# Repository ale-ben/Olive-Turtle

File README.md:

- [1. Olive-Turtle](#1-olive-turtle)
- [2. Final Result](#2-final-result)
	- [2.1. Dashboard](#21-dashboard)
	- [2.2. Debug Dashboard](#22-debug-dashboard)
- [3. Required components and software](#3-required-components-and-software)
	- [3.1. Home Assistant](#31-home-assistant)
		- [3.1.1. Hardware](#311-hardware)
		- [3.1.2. Software](#312-software)
	- [3.2. MicroController](#32-microcontroller)
		- [3.2.1. Hardware](#321-hardware)
		- [3.2.2. Software](#322-software)
- [4. Installation and wiring](#4-installation-and-wiring)
	- [4.1. Home Assistant](#41-home-assistant)
	- [4.2. Microcontroller](#42-microcontroller)
		- [4.2.1. Wiring](#421-wiring)
		- [4.2.2. Software](#422-software)
			- [4.2.2.1. Test Software](#4221-test-software)
			- [4.2.2.2. ESPHome integration](#4222-esphome-integration)
- [5. Telegram Bot](#5-telegram-bot)
	- [5.1. Bot Configuration](#51-bot-configuration)
	- [5.2. Commands](#52-commands)
- [6. Future Development](#6-future-development)
	- [6.1. Hardware Side](#61-hardware-side)
	- [6.2. Software Side](#62-software-side)

# 1. Olive-Turtle

 Turtle as a logo, no background, realistic")

Olive Turtle is a project developed for the "Laboratory of Making" course (2022/2023) taught by Professor Renzo Davoli and Professor Federico Montori at the University of Bologna.

The project aims to implement a board capable of controlling a 12V LED strip with brightness control and environmental data acquisition.

Everything is controlled using Home Assistant, an open source software written in Python and released in 2013 under the Apache 2.0 license. It is a complete home automation system that can integreate with most existing IoT and home automation devices (mainly thanks to the huge user base) and be used to control and automate all the devices in your home, including custom made microcontroller boards.

# 2. Final Result

## 2.1. Dashboard

> Note that due to technical problems with the sensors air quality values are not available in this screenshot.

The resulting dashboard integrates the existing "smart lights" (Ikea TRADFRI) and the Olive Turtle board, which is used to control the LED strip and acquire environmental data.

The board allows for a quick glance at the system status or a more detailed view of the data, and it can be used to control the LED strip brightness.

## 2.2. Debug Dashboard

In the debug section you can see raw data from the board along with some debug parameters like WiFi signal strength.

# 3. Required components and software

## 3.1. Home Assistant
### 3.1.1. Hardware
- Raspberry PI 3 (or newer). Note that Home Assistant specifically says that PI 3 is borderline supported due to the limited resources, but it works fine for this project.
### 3.1.2. Software
- [Home Assistant](https://www.home-assistant.io/installation/)
- [Raspberry PI Imager](https://www.raspberrypi.org/software/)

## 3.2. MicroController
### 3.2.1. Hardware
- ESP32 (or any other microcontroller capable of WiFi communication)
- Sensors
  - BMP280
  - ENS160+AHT2x
- LED Control
  - IRF520N MOSFET
  - TLP621 Optocoupler
  - Various resistors
- LED strip with 12V power supply
### 3.2.2. Software
- [Python3](https://www.python.org/downloads/)
- [PlatformIO](https://platformio.org/platformio-ide)
- [ESPHome CLI](https://esphome.io/guides/getting_started_command_line.html)

# 4. Installation and wiring
## 4.1. Home Assistant
If you are using Home Assistant, installation is pretty straight forward, in PI Imager OS selection choose _other specific-purpose OS_, then _Home Assistant and Home Automation_ and finally _Home Assistant_, configure Wireless (If needed) and flash the image on the SD card.

Home Assistant will be available after a couple of minutes at `http://homeassistant.local:8123` (or `http://<ip_address>:8123` if you don't have mDNS enabled on your network).

> Home Assistant is a very complex software, and it's not the focus of this guide, so I won't go into details on how to configure it, but you can find a lot of guides on the internet.

Once installed, you can install ESPHome from the Home Assistant Add-on Store, and then you can start configuring your ESP32 board:
1. Go to the ESPHome tab in Home Assistant sidebar
2. Click on the + button in the bottom right corner
3. Give the board a name
4. Select the board type (ESP32)

ESPHome will generate a configuration file for you and prepare everything for the first upload.

> Note that theoretically the microcontroller setup could be done entirely from this page but it is not a viable option in this specific case due to two problems:
> - We have a component not available (yet) in the ESPHome library;
> - In my tests I noticed that Raspberry PI 3 does not have enough power to compile and upload the code to the board (would probavly work with a Raspberry PI 4).

## 4.2. Microcontroller

### 4.2.1. Wiring
This repository provides both a wiring diagram and a proposed implementation for splitting the component across multiple protoboards.

The `schematics` folder contains the KiCAD project for the wiring diagram and the VeroRoute project for the protoboard implementation. The wiring is consistent between the two projects.

The wiring diagram is split in three sections, the first one contains the microcontroller and relative connections, the second the sensors and I2C connections to the controller and the third the LED strip and relative connections.

This is the proposed implementation for the protoboard, all sensor identification codes refer to the one used in the KiCAD schematic:
> Note that all images have a mirrored version, so that you can use them as a reference when soldering the components on the back of the board. This version can be found in the `schematics/Olive-Turtle_VeroRoute/png` folder.

**Main Board**

**Sensor Board**

**LED Board**

### 4.2.2. Software

#### 4.2.2.1. Test Software
The `Olive-Turtle_manual_control` folder contains a simple test software that can be used to verify that all the components are working correctly.

Make sure to have PlatformIO installed and open the project folder, then using the PlatformIO UI you can compile and upload the code to the board.

This version of the software does not have any WiFi or Home Assistant integration, it simply reads the sensors and allows you to control the LED strip using the serial monitor.
After setup complete this is the list of available commands:
- `help`: Print the list of available commands
- `led <value>`: Set the LED brightness to the specified value (0-255)
- `led`: Print the current LED brightness
- `aht` | `bmp` | `ens`: Print the current value of the specified sensor
- `all`: Print the current value of all the sensors

After verifying that all sensors provide correct values and that the LED strip is working, you can proceed to the next step and configure the board to work with Home Assistant.

> Note that the test software is not required for the next step, it is only provided as a way to verify that all the components are working correctly.

#### 4.2.2.2. ESPHome integration

This is the final step, we will now configure the board to work with Home Assistant.

Open the `Olive-Turtle_esphome` folder, rename (or copy) the secretsTemplate.yaml to secrets.yaml and fill in the required information.
One of the fields will be `homeassistant_key`, this key can be found in Home Assistant, in the ESPHome tab by clicking on the three dots next to the board name and then on _Show API Key.

Once you have filled in all the required information, you can compile and upload the code to the board with `esphome run Olive-Turtle.yaml`.
> Note that the first upload MUST be done using a USB cable, after the first upload you can use OTA updates.

If everything went correctly you should see the board as online in Home Assistant. Next go to settings and add the board as a device. The board will be automatically added to the auto generated dashboard and you can now control the LED strip and see the sensor values.

# 5. Telegram Bot
As a proof of concept I tried implementing a Telegram Bot ([@OliveTurtleBot](https://t.me/OliveTurtleBot)) using the Telegram extension of Home Assistant.

The bot is very simple, it allows you to activate two predefined scenes, __away__ and __nightpc__, but can also be used to get notifications from other Home Assitant automations.

Unfortunately the Telegram extension does not have a UI setup process, so you have to manually edit the configuration file, but it is not very complicated and is explained in the [official documentation](https://www.home-assistant.io/integrations/telegram).

## 5.1. Bot Configuration
The first step is to edit `/config/configuration.yaml` and add the following lines while replacing the placeholders (elements between [[  ]] ) with your data:
```yaml
# Telegram Bot
telegram_bot:
  - platform: polling
    api_key: "[[ API KEY ]]"
    allowed_chat_ids:
      - [[ CHAT ID ]]

# Notifier
notify:
  - platform: telegram
    name: "[[ NAME ]]" # This can be anything you want, will be used internally when calling in automations
    chat_id: [[ CHAT ID]]
```

By adding this to configuration we set up two things:

1. We enable the Telegram Bot extension and configure it to use polling (instead of webhooks) and we specify the API key (provided by [@BotFather](https://t.me/BotFather)) and the chat ID (if you don't know your chat id, use [@getidsbot](https://t.me/getidsbot)).
2. We set up a notify action that we can use in our automations. This will allow us to send messages from the bot to a specific user (as per telegram rules, the user MUST have started the bot first).

After this we need to reload Home Assistant YAML, we can do so from the YAML tab by pressing restart and quick restart.

To test notifications you can use the developer tools in Home Assistant, go to the services tab and select `notify.[[ NAME ]]` from the dropdown menu, then fill in the message and click on call service. You should receive a message from the bot.

Now the bot is able to send messages to the user but it ignores everything received from the user.

## 5.2. Commands
The bot is able to receive commands from the user, but it needs to know what to do with them. To do this we need to add a new automation.

For the sake of this documentation, we will only implement the __ping__ command since th implementation is the same for all the other commands.

Despite what the [official documentation](https://www.home-assistant.io/integrations/telegram_bot/#event-triggering) says, it's easier to configure this from the UI rather than from the automation file.
To do so, go to settings and then to automations, click on the + button, create new automation and select the following options:
- As trigger select a manual trigger
  - insert `telegram_command` as event type
  - insert `command: /ping` as event data
- As action select call service
  - select `Notifications: Send a notification with [[name]]`
  - as message write `pong`

Click save in the bottom right corner and give it a name, once this is done you can test the command by sending `/ping` to the bot.

If you want the bot to suggest available commands you can manually set them using [@BotFather](https://t.me/BotFather).

To make a command that activates a scene you just have to add a second action in your automation and select scene as you can see in the following image:

# 6. Future Development
## 6.1. Hardware Side
- [ ] https://github.com/ale-ben/Olive-Turtle/issues/4 Fix Air quality sensor or identify valid alternative
- [ ] Prototype and print first PCB version
## 6.2. Software Side
- [ ] As soon as https://github.com/esphome/esphome/pull/4243 is merged, remove custom ENS160 implementation and use library instead
  - Removing the custom implementation would also allow to upload directly from Home Assistant (with a more powerful server) therefore removing entirely the need for ESPHome CLI
- [X] Implement InfluxDB as long term sensor data storage
- [ ] Implement Grafana as a dashboard alternative

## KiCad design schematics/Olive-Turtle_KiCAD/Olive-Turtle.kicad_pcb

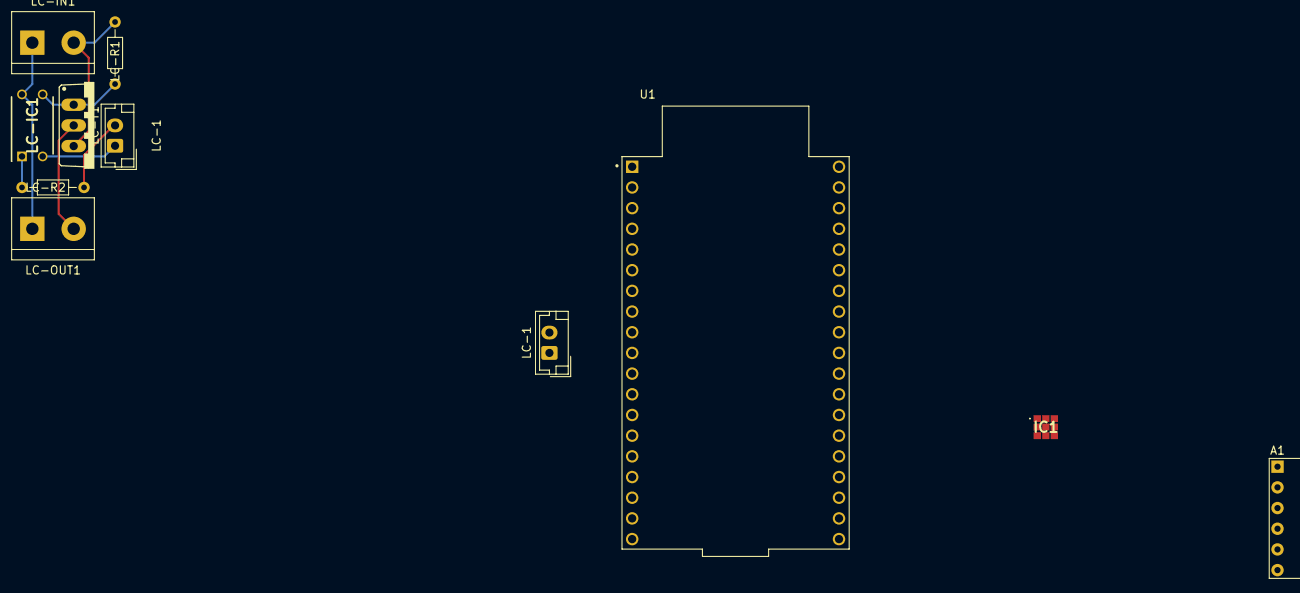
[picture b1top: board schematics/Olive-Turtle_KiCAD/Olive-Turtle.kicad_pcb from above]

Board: 2 copper layers, 11 parts (0 on the bottom side), 13 nets.

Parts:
A1: BMP280_Module
IC1: ENS160-BGLT; ENS160BGLT
LC-1, LC-1#2: JST 2.5mm 2P Wafer; JST_EH_B2B-EH-A_1x02_P2.50mm_Vertical
LC-IC1: TLP621; DIP762W60P254L460H450Q4N
LC-IN1: Screw_Terminal_01x02; TerminalBlock_bornier-2_P5.08mm
LC-OUT1: Screw_Terminal_01x02; TerminalBlock_bornier-2_P5.08mm
LC-R1: 2.2k R; R_Axial_DIN0204_L3.6mm_D1.6mm_P7.62mm_Horizontal
LC-R2: 330 R; R_Axial_DIN0204_L3.6mm_D1.6mm_P7.62mm_Horizontal
LC-T1: IRF520; TO220BV
U1: ESP32-DEVKITC-32U; MODULE_ESP32-DEVKITC-32U

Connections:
/LC1-G: LC-1#2.1, U1.14 (GND1)
/LC1-S: LC-1#2.2, U1.6 (IO35)
/LED Control/12V: LC-IC1.4 (C), LC-IN1.1, LC-OUT1.1
/LED Control/GND: LC-IN1.2, LC-R1.1, LC-T1.S
/LED Control/LC-G: LC-1.1, LC-IC1.2 (K)
/LED Control/LC-S: LC-1.2, LC-R2.2
/SCL: A1.3 (SCL), IC1.2 (SCLK_/_SCL), U1.36 (IO22)
/SDA: A1.4 (SDA), IC1.1 (MOSI_/_SDA), U1.33 (IO21)
unnamed: A1.2 (GND), IC1.8 (VSS_1), U1.38 (GND3)
unnamed: A1.1 (VCC), IC1.5 (VDDIO), U1.1 (3V3)
unnamed: LC-IC1.1 (A), LC-R2.1
unnamed: LC-IC1.3 (E), LC-R1.2, LC-T1.G
unnamed: LC-OUT1.2, LC-T1.D

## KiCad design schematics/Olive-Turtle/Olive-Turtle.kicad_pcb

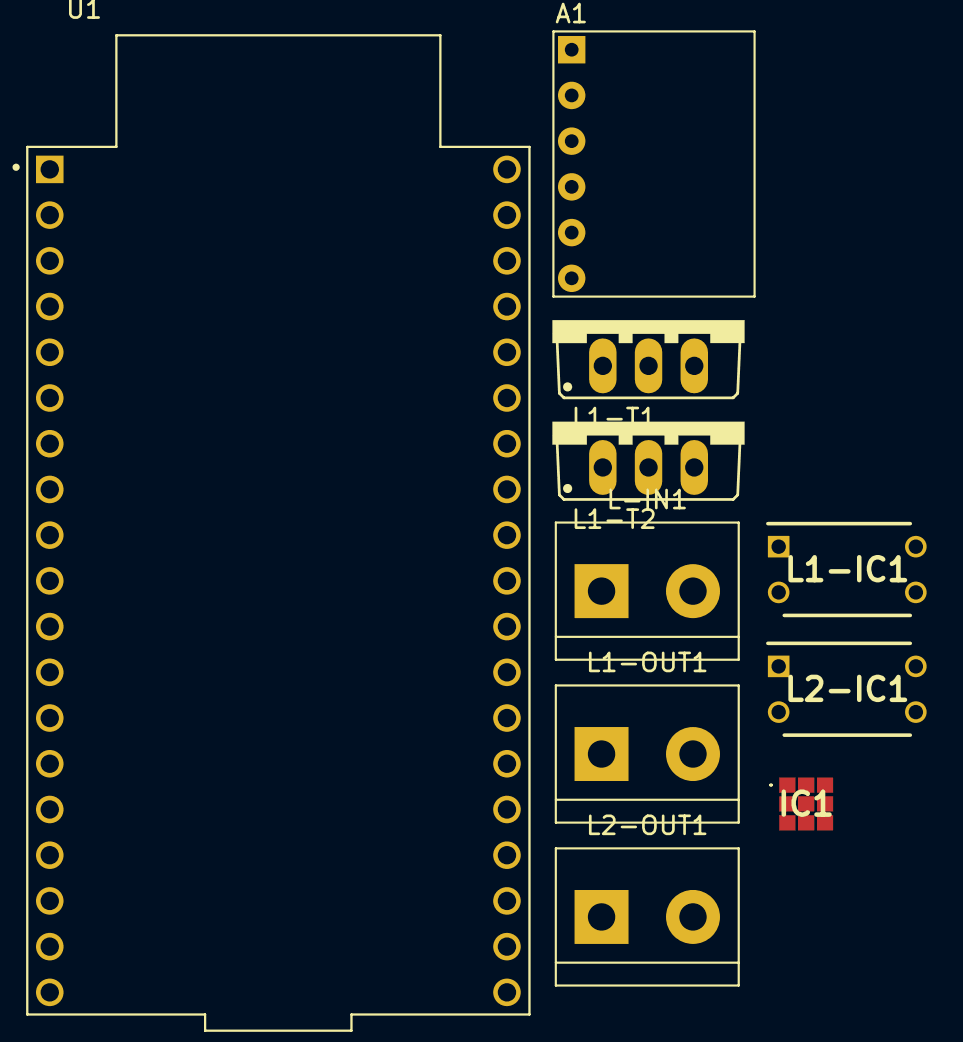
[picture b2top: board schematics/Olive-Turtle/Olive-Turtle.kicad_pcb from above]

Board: 2 copper layers, 10 parts (0 on the bottom side), 11 nets, no tracks yet.

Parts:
A1: BMP280_Module
IC1: ENS160-BGLT; ENS160BGLT
L1-IC1, L2-IC1: TLP621; DIP762W60P254L460H450Q4N
L1-OUT1, L2-OUT1: Screw_Terminal_01x02; TerminalBlock_bornier-2_P5.08mm
L1-T1, L1-T2: IRF520; TO220BV
L-IN1: Screw_Terminal_01x02; TerminalBlock_bornier-2_P5.08mm
U1: ESP32-DEVKITC-32U; MODULE_ESP32-DEVKITC-32U

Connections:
/12V: L1-IC1.4 (C), L1-OUT1.1, L2-IC1.4 (C), L2-OUT1.1, L-IN1.1
/GND: L1-T1.S, L1-T2.S, L-IN1.2
/SCL: A1.3 (SCL), IC1.2 (SCLK_/_SCL), U1.36 (IO22)
/SDA: A1.4 (SDA), IC1.1 (MOSI_/_SDA), U1.33 (IO21)
unnamed: A1.2 (GND), IC1.8 (VSS_1), U1.38 (GND3)
unnamed: A1.1 (VCC), IC1.5 (VDDIO), U1.1 (3V3)
unnamed: L1-IC1.3 (E), L1-T2.G
unnamed: L1-IC1.2 (K), L2-IC1.2 (K), U1.14 (GND1)
unnamed: L1-OUT1.2, L1-T2.D
unnamed: L1-T1.G, L2-IC1.3 (E)
unnamed: L1-T1.D, L2-OUT1.2

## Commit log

2023-09-11 [develop] Project restart
2023-09-11 Designed VeeCAD schematic
2023-09-12 [develop] Schematic for LC
2023-09-18 [develop] Update Kicad schematic
2023-09-19 [develop] Reset OT manual control
2023-09-19 [develop] Remove old schematics
2023-09-19 [develop] Get & set LED PWM
2023-09-19 [develop] Working ?
2023-09-19 [develop] Move LED1 to pin 32 since 35 is input only
2023-09-19 [develop] Started esphome
2023-09-19 [develop] Implemented WiFi Secrets
2023-09-20 [develop] First Sensor implementation
2023-09-20 [develop] ENS160 sensor implementation
2023-09-20 [develop] Sensor fix
2023-09-21 [develop] Add led to control circuit
2023-09-21 [develop] Fix TLP polarity
2023-09-24 [develop] Removed LED from LED Control circuit
2023-09-24 [develop] ProtoBoards for all other boards + refactor sch
2023-09-27 [develop] Update mainboard scheme and move export to separate folder
2023-10-01 [develop] Update ENS160 lib
2023-10-04 [develop] Added logo
2023-10-04 [documentation] Added generation params
2023-10-04 [documentation] test
2023-10-04 [documentation] svg
2023-10-04 [documentation] documentation
2023-10-04 [documentation] Update
2023-10-09 [documentation] Dashboard
2023-10-09 [documentation] debug dashboard
2023-10-09 [documentation] Automation guide
2023-10-09 Link future with issue
2023-10-09 [develop] Add section numbers
2023-10-10 [develop] Send AHT even if ENS not working
2023-10-18 fix: Olive-Turtle_esphome/requirements.txt to reduce vulnerabilities
    The following vulnerabilities are fixed by pinning transitive dependencies:
    - https://snyk.io/vuln/SNYK-PYTHON-URLLIB3-6002459
2023-10-26 fix: Olive-Turtle_esphome/requirements.txt to reduce vulnerabilities
    The following vulnerabilities are fixed by pinning transitive dependencies:
    - https://snyk.io/vuln/SNYK-PYTHON-CRYPTOGRAPHY-6036192
2023-11-29 fix: Olive-Turtle_esphome/requirements.txt to reduce vulnerabilities
    The following vulnerabilities are fixed by pinning transitive dependencies:
    - https://snyk.io/vuln/SNYK-PYTHON-CRYPTOGRAPHY-6092044
